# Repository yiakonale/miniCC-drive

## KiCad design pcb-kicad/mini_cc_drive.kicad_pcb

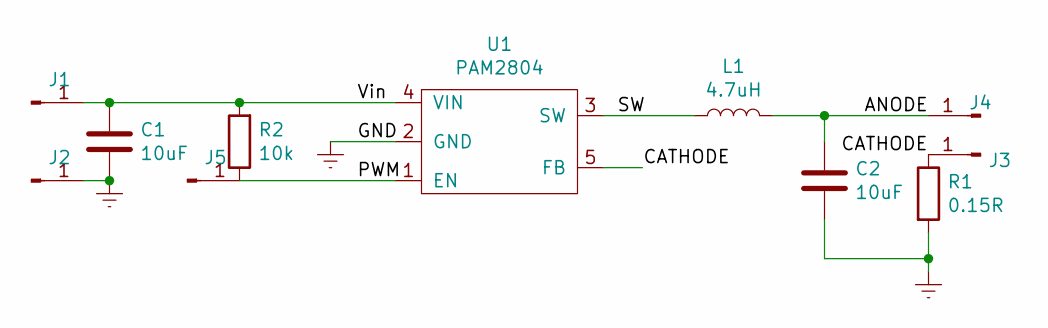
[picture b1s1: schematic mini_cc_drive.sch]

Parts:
C1, C2: 10uF; C_1206_3216Metric
J1, J2, J3, J4, J5: Conn_01x01_Male; PinHeader_1x01_P2.54mm_Vertical
L1: 4.7uH; L_1008_2520Metric
R1: 0.15R; R_2512_6332Metric
R2: 10k; R_1206_3216Metric
U1: PAM2804; TSOT-23-5_HandSoldering

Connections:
/ANODE: C2.1, J4.1, L1.2
/CATHODE: J3.1, R1.1, U1.5 (FB)
/PWM: J5.1, R2.1, U1.1 (EN)
/SW: L1.1, U1.3 (SW)
/Vin: C1.1, J1.1, R2.2, U1.4 (VIN)
Earth: C1.2, C2.2, J2.1, R1.2, U1.2 (GND)

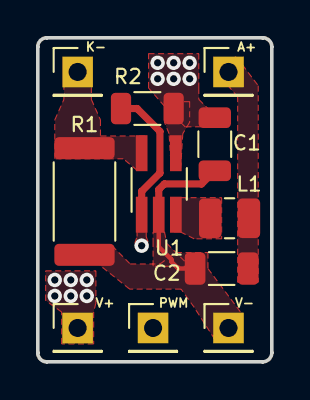
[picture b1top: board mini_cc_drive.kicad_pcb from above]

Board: 2 copper layers, 13.0 x 18.0 mm, 11 parts (0 on the bottom side), 6 nets.

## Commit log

2024-06-21 kicad pcb project
2024-06-21 init
